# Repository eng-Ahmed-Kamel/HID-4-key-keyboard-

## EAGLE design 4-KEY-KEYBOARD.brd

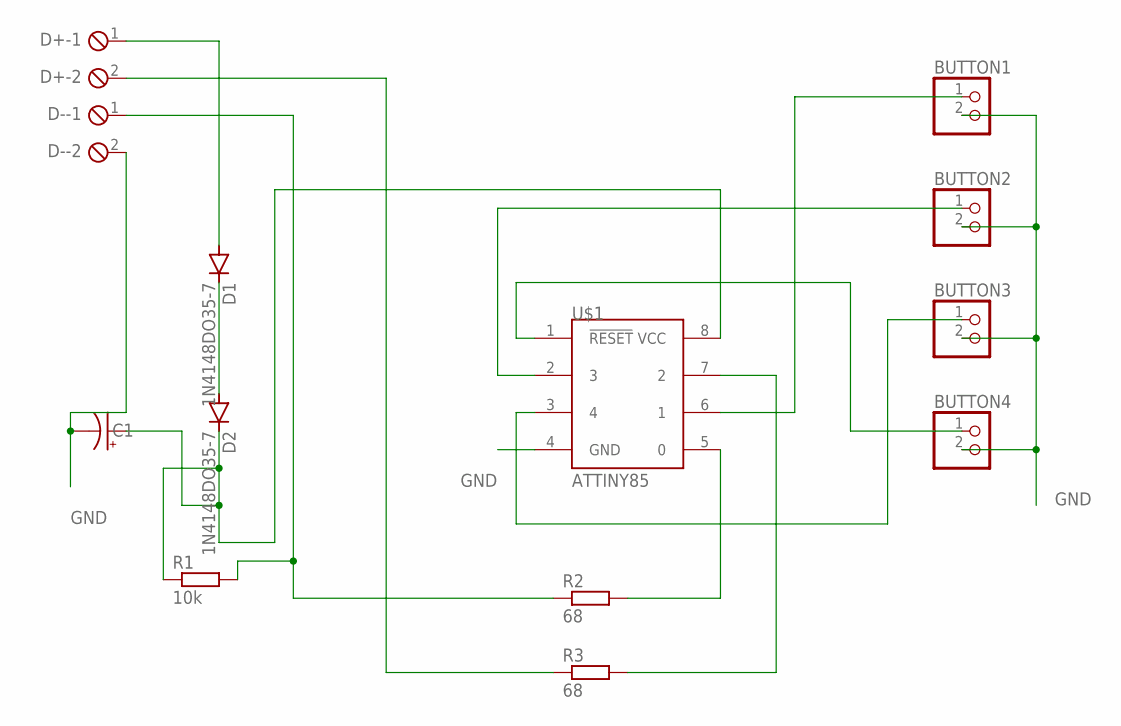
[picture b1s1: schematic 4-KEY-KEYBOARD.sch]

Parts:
BUTTON1, BUTTON2, BUTTON3, BUTTON4: PINHD-1X2; 1X02
C1: CPOL-USE2.5-6; E2,5-6
D1, D2: 1N4148DO35-7; DO35-7
D+: MPT2; 2POL254
D-: MPT2; 2POL254
R1: 10k; 0204/7
R2, R3: 68; 0204/7
U$1: ATTINY85; 8P3

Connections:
GND: BUTTON1.2, BUTTON2.2, BUTTON3.2, BUTTON4.2, C1.-, D-.2, U$1.4 (GND)
unnamed: BUTTON1.1, U$1.6 (1)
unnamed: BUTTON2.1, U$1.2 (3)
unnamed: BUTTON3.1, U$1.3 (4)
unnamed: BUTTON4.1, U$1.1 (!RESET)
unnamed: D1.A, D+.1
unnamed: D1.C, D2.A
unnamed: C1.+, D2.C, R1.1, U$1.8 (VCC)
unnamed: R2.2, U$1.5 (0)
unnamed: D-.1, R1.2, R2.1
unnamed: R3.2, U$1.7 (2)
unnamed: D+.2, R3.1

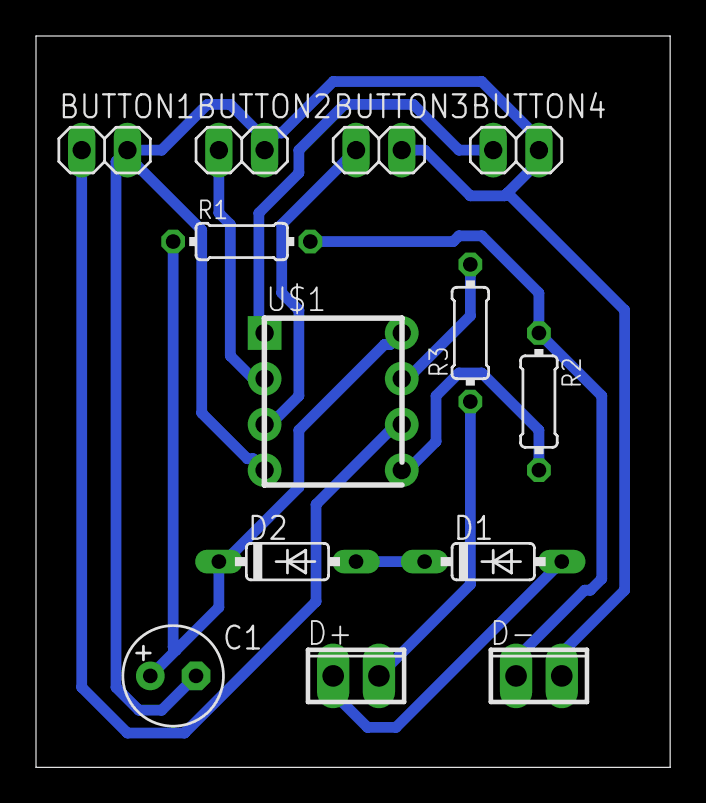
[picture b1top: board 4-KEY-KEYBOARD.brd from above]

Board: 2 copper layers, 35.2 x 40.6 mm, 13 parts (0 on the bottom side), 12 nets.
